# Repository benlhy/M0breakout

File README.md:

# M0+ breakout
M0+ Breakout Board

This breakout board combines both the Adafruit M0 Feather and the Sparkfun board. From the Adafruit board comes Lipo charging, and from the Sparkfun board comes the full breakout. The header pins for SWO programming are broken out, and a microUSB interface is provided just in case you do compile your own bootloader.

# Bootloaders
Both companies have provided tools to create their bootloaders. However do note that you'll have to use your own VID/PID for USB if you are planning to use it in your own products. The Adafruit bootloader is preferred since it is more up to date.

# Firmware references
1. https://learn.adafruit.com/compiling-m0-atsamd21-bootloader/compile
2. https://github.com/adafruit/Adafruit-Feather-M0-Basic-Proto-PCB
3. https://github.com/sparkfun/SAMD21_Dev_Breakout
4. https://github.com/sparkfun/SAMD21_Mini_Breakout

# Thanks
Adafruit and Sparkfun invests time and resources in providing open designs. This project would not have been possible without their guides. Support Adafruit and Sparkfun and open-source hardware by purchasing products from them!

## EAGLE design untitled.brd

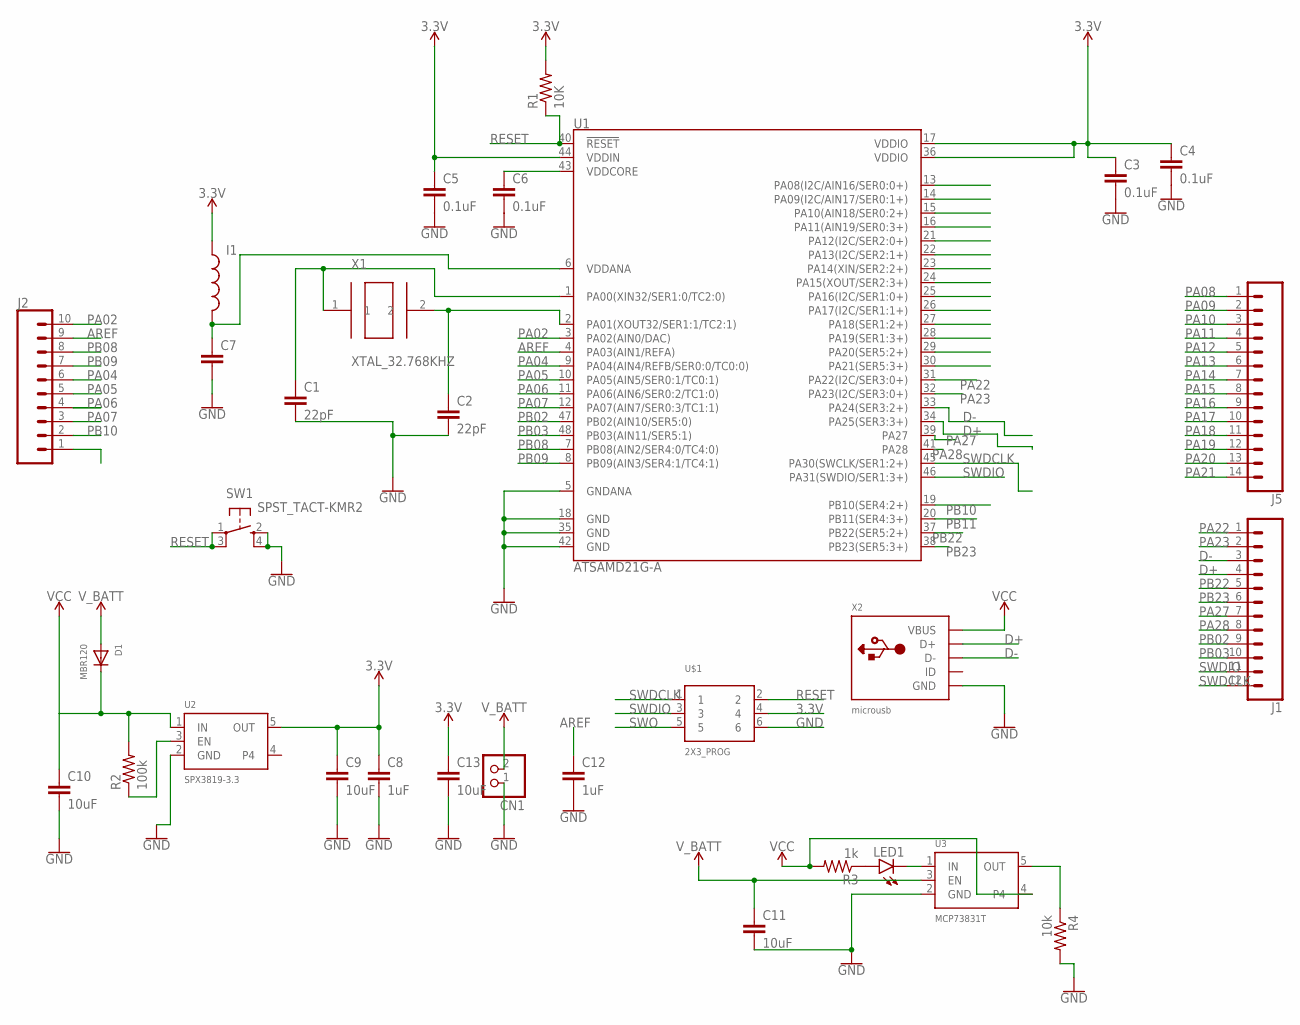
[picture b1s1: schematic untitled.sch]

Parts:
C1, C2: 22pF; 0805
C3, C4, C5, C6: 0.1uF; 0805
C7: CAP; 0805
C8, C12: 1uF; 0805
C9, C10, C11, C13: 10uF; 0805
CN1: JST_2PIN; JSTPH2
D1: MBR120; SOD-123
I1: IND; 0805
J1: CONN_12; 1X12
J2: CONN_10"; 1X10
J5: CONN_14; 1X14
LED1: LED0603; LED-0603
R1: 10K; 0805
R2: 100k; 0805
R3: 1k; 0805
R4: 10k; 0805
SW1: SPST_TACT-KMR2; KMR2
U1: ATSAMD21G-A; TQFP-48
U2: SPX3819-3.3; SOT23-5
U3: MCP73831T; SOT23-5
U$1: 2X3_PROG; 2X3-SMD_PROG
X1: XTAL_32.768KHZ; ABS07-32.768KHZ-9-T
X2: microusb; 4UCONN_20329_V2

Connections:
3.3V: C3.1, C4.1, C5.1, C8.1, C9.1, C13.1, I1.1, R1.2, U1.17 (VDDIO), U1.36 (VDDIO), U1.44 (VDDIN), U2.5 (OUT), U$1.4
AREF: C12.1, J2.9, U1.4 (PA03(AIN1/REFA))
D+: J1.4, U1.34 (PA25(SER3:3+)), X2.D+
D-: J1.3, U1.33 (PA24(SER3:2+)), X2.D-
GND: C1.2, C2.2, C3.2, C4.2, C5.2, C6.2, C7.2, C8.2, C9.2, C10.2, C11.2, C12.2, C13.2, CN1.1, R4.2, SW1.2 (S), SW1.4 (S1), U1.5 (GNDANA), U1.18 (GND), U1.35 (GND), U1.42 (GND), U2.2 (GND), U3.2 (GND), U$1.6, X2.BASE@1 (GND), X2.BASE@2 (GND), X2.GND, X2.SPRT@1 (GND), X2.SPRT@2 (GND), X2.SPRT@3 (GND), X2.SPRT@4 (GND)
unnamed: C1.1, U1.1 (PA00(XIN32/SER1:0/TC2:0)), X1.1
unnamed: C2.1, U1.2 (PA01(XOUT32/SER1:1/TC2:1)), X1.2
unnamed: C6.1, U1.43 (VDDCORE)
unnamed: C7.1, I1.2, U1.6 (VDDANA)
unnamed: R2.1, U2.3 (EN)
unnamed: LED1.A, R3.1
unnamed: LED1.C, U3.1 (IN)
unnamed: R4.1, U3.5 (OUT)
PA02: J2.10, U1.3 (PA02(AIN0/DAC))
PA04: J2.6, U1.9 (PA04(AIN4/REFB/SER0:0/TC0:0))
PA05: J2.5, U1.10 (PA05(AIN5/SER0:1/TC0:1))
PA06: J2.4, U1.11 (PA06(AIN6/SER0:2/TC1:0))
PA07: J2.3, U1.12 (PA07(AIN7/SER0:3/TC1:1))
PA08: J5.1, U1.13 (PA08(I2C/AIN16/SER0:0+))
PA09: J5.2, U1.14 (PA09(I2C/AIN17/SER0:1+))
PA10: J5.3, U1.15 (PA10(AIN18/SER0:2+))
PA11: J5.4, U1.16 (PA11(AIN19/SER0:3+))
PA12: J5.5, U1.21 (PA12(I2C/SER2:0+))
PA13: J5.6, U1.22 (PA13(I2C/SER2:1+))
PA14: J5.7, U1.23 (PA14(XIN/SER2:2+))
PA15: J5.8, U1.24 (PA15(XOUT/SER2:3+))
PA16: J5.9, U1.25 (PA16(I2C/SER1:0+))
PA17: J5.10, U1.26 (PA17(I2C/SER1:1+))
PA18: J5.11, U1.27 (PA18(SER1:2+))
PA19: J5.12, U1.28 (PA19(SER1:3+))
PA20: J5.13, U1.29 (PA20(SER5:2+))
PA21: J5.14, U1.30 (PA21(SER5:3+))
PA22: J1.1, U1.31 (PA22(I2C/SER3:0+))
PA23: J1.2, U1.32 (PA23(I2C/SER3:0+))
PA27: J1.7, U1.39 (PA27)
PA28: J1.8, U1.41 (PA28)
PB02: J1.9, U1.47 (PB02(AIN10/SER5:0))
PB03: J1.10, U1.48 (PB03(AIN11/SER5:1))
PB08: J2.8, U1.7 (PB08(AIN2/SER4:0/TC4:0))
PB09: J2.7, U1.8 (PB09(AIN3/SER4:1/TC4:1))
PB10: J2.2, U1.19 (PB10(SER4:2+))
PB11: J2.1, U1.20 (PB11(SER4:3+))
PB22: J1.5, U1.37 (PB22(SER5:2+))
PB23: J1.6, U1.38 (PB23(SER5:3+))
RESET: R1.1, SW1.1, SW1.3 (P1), U1.40 (!RESET!), U$1.2
SWDCLK: J1.12, U1.45 (PA30(SWCLK/SER1:2+)), U$1.1
SWDIO: J1.11, U1.46 (PA31(SWDIO/SER1:3+)), U$1.3
SWO: U$1.5
VCC: C10.1, D1.C, R2.2, R3.2, U2.1 (IN), U3.4, X2.VBUS
V_BATT: C11.1, CN1.2, D1.A, U3.3 (EN)

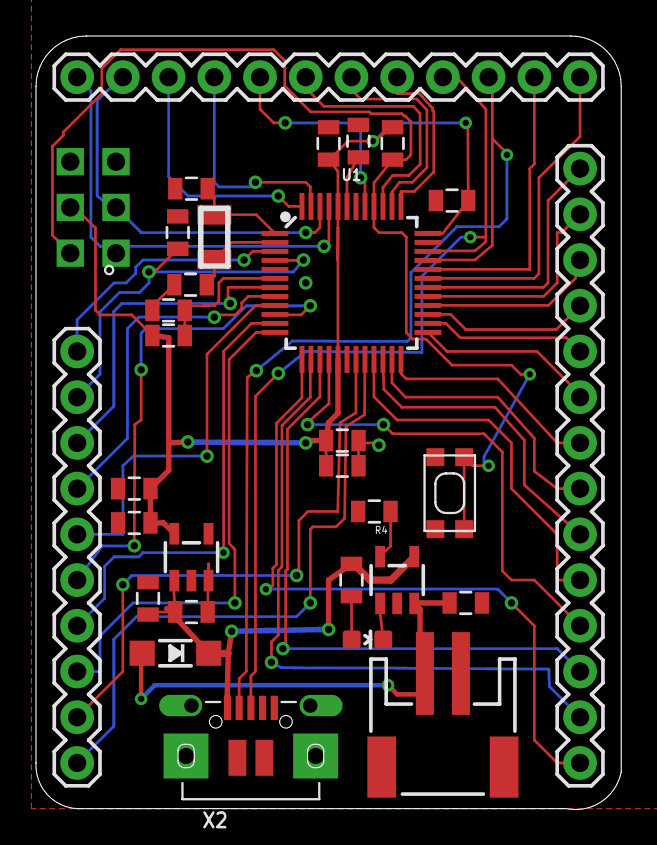
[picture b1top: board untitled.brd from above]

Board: 2 copper layers, 32.5 x 43.0 mm, 31 parts (0 on the bottom side), 49 nets.

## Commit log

2017-07-10 Initial upload
2017-07-10 Update LICENSE
2017-08-02 update Readme and boards
    Boards updated to reduce vias and moved the reset button location

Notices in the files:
parts and their libraries:
SparkFun-Connectors: Licensing: Creative Commons ShareAlike 4.0 International - https://creativecommons.org/licenses/by-sa/4.0
microbuilder: This work is placed in the public domain, and may be freely used for commercial and non-commercial work with the following conditions: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
